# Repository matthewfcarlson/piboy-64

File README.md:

# Piboy-64
Original designed by Matthew Carlson
Huge shout out to /u/Ryzee and his GBA project here: https://github.com/Ryzee119/GBA_Emulator-by-Ryzee119-/blob/master/README.md

This is a true N64/PS1 emulator stuffed inside a GBA case. Based around a Raspberry Pi compute module 3 which is smaller but has the same guts as a RPi 3. A zero just didn't seem to cut it. Perhaps in the future, I'll do another version with the zero inside as well but for now I'll stick with this.

Details of how to build this and photos can be found on https://hackaday.io/project/17935-piboy-64

##DISCLAIMER:
This is a complex board with lots of parts. Make sure you know what you're doing. Surface mount soldering isn't hard but it is not for beginners. I used a third party replacement case for my GBA body and they vary from vendor to vendor so be flexible if what you have is different than what I did.

I take no responsibility for the following:

1.	You went ahead and purchased everything, soldered it up and it didn’t work because reasons.
2.	You soldered an SMD chip and done broke the pins.
3.	If a component in the BOM is not available or becomes obsolete, use your best judgement to find a replacement. I highly recommend parts.io which can provide risk factors and compatible chips.
4.	A component is missing from the BOM or you ordered parts you didn't need. (Look at the schematic before ordering)
5.	The thing burst into flame and explodes in your hands and burns your house down.
6.	It doesn’t fit in your GBA case

Any advice and support I provide from this point is purely out of the kindness of my heart.

## Issues Observed with this revision:
None yet

## Making your own
So you read this whole thing and still want to make your own? Well. Let's get started then. Visiting the hackaday.io link will give you detailed build instructions. I'll try and document as I go.

Good luck.

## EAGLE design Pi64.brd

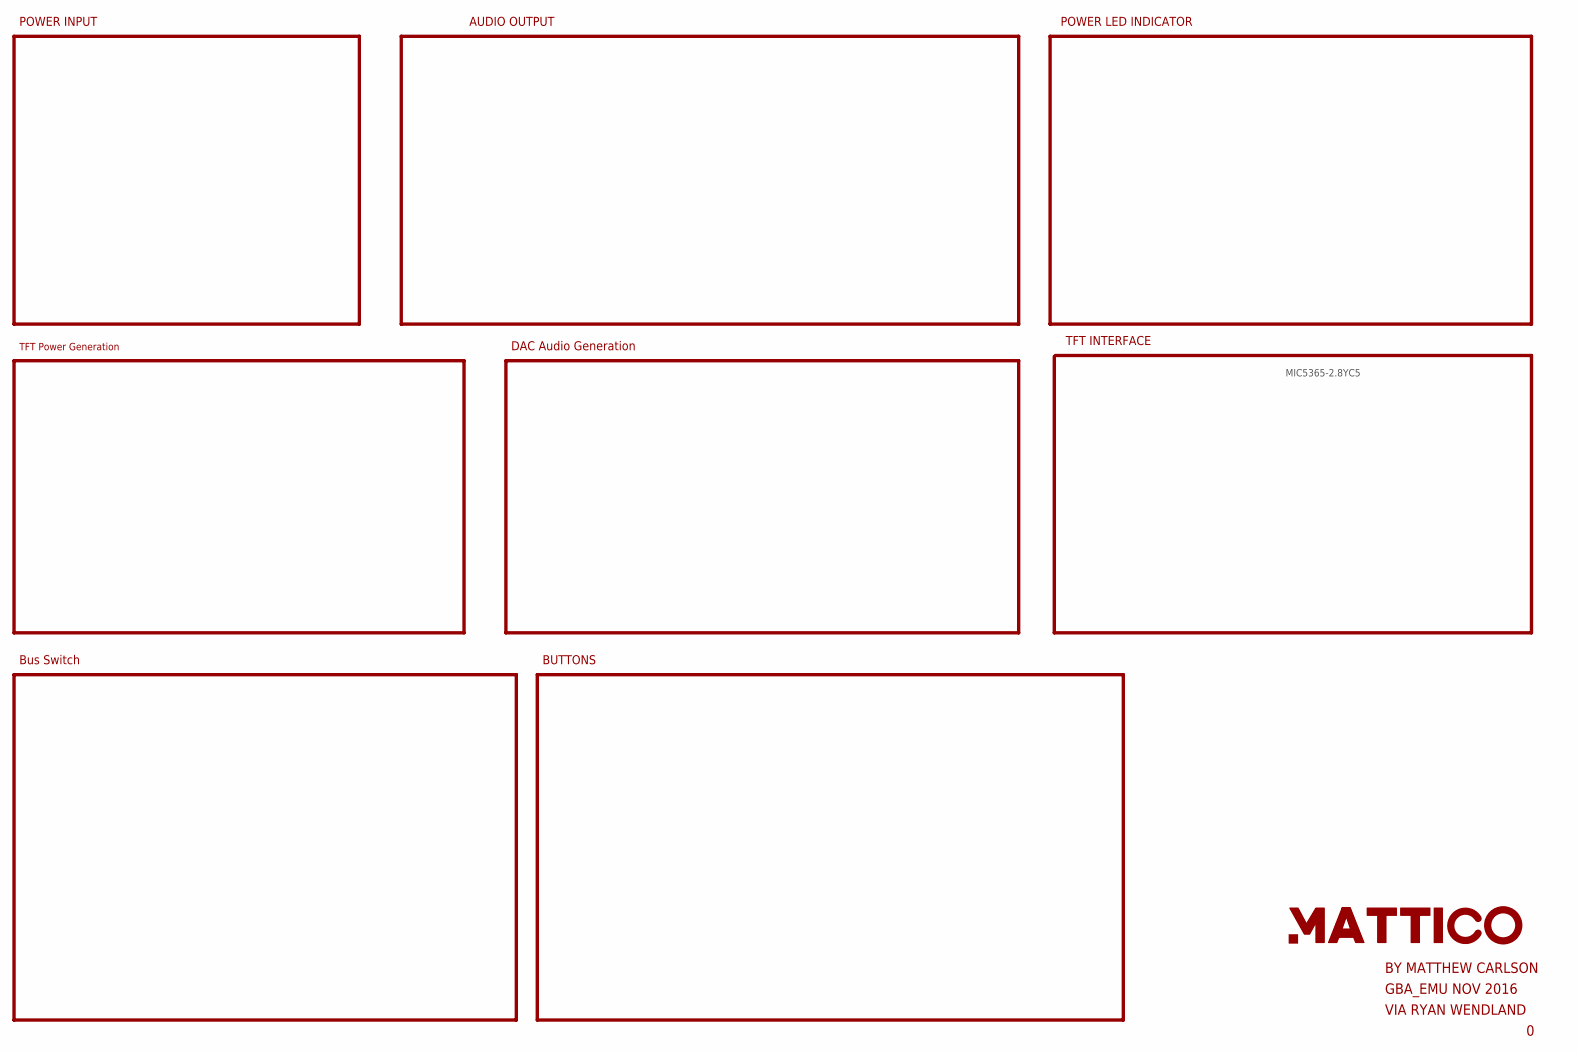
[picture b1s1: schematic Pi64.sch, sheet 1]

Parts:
U$2: LOGO2INCH_SVG; LOGO_2INCH_SVG

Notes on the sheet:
POWER LED INDICATOR
AUDIO OUTPUT
POWER INPUT
TFT INTERFACE
GBA_EMU NOV 2016
VIA RYAN WENDLAND
BY MATTHEW CARLSON
BUTTONS
MIC5365-2.8YC5
DAC Audio Generation
Bus Switch
TFT Power Generation

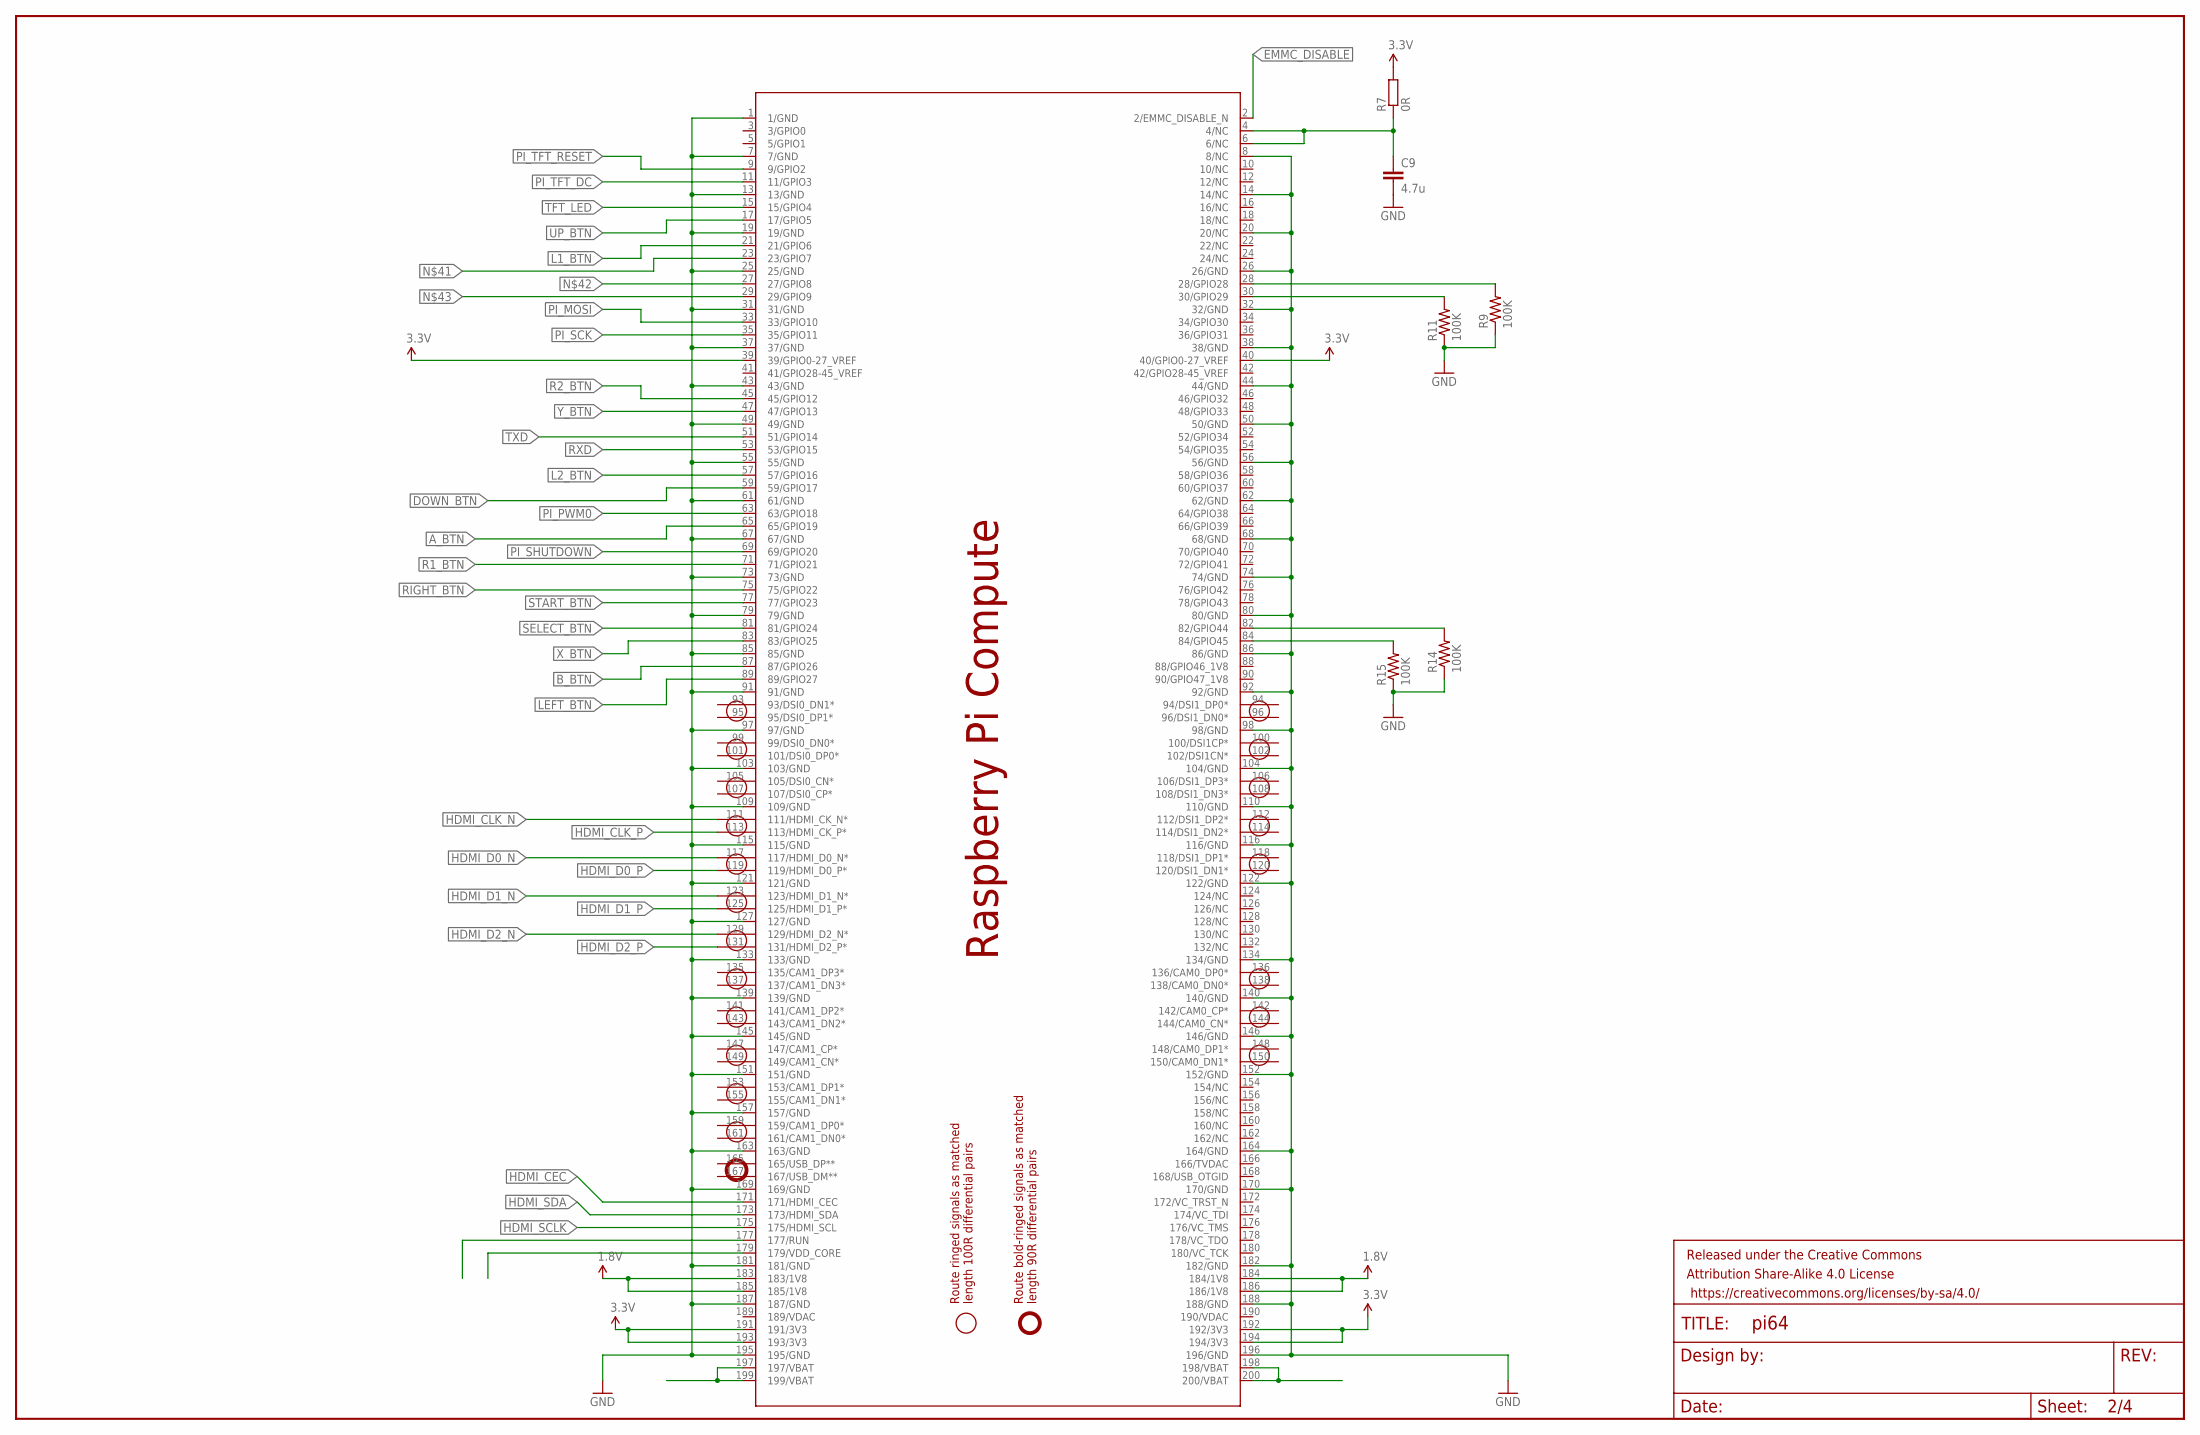
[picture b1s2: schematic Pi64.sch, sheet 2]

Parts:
C9: 4.7u; C1608
FRAME2: FRAME-LEDGER; CREATIVE_COMMONS
PCB1: RPI_COMPUTE
R7: 0R; R2012
R9, R11, R14, R15: 100K; R0805

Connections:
1.8V: PCB1.183 (183/1V8), PCB1.184 (184/1V8), PCB1.185 (185/1V8), PCB1.186 (186/1V8); also elsewhere on the board
3.3V: PCB1.39 (39/GPIO0-27_VREF), PCB1.40 (40/GPIO0-27_VREF), PCB1.191 (191/3V3), PCB1.192 (192/3V3), PCB1.193 (193/3V3), PCB1.194 (194/3V3), R7.2; also elsewhere on the board
A_BTN: PCB1.65 (65/GPIO19)
B_BTN: PCB1.87 (87/GPIO26)
DOWN_BTN: PCB1.59 (59/GPIO17)
EMMC_DISABLE: PCB1.2 (2/EMMC_DISABLE_N)
GND: C9.2, PCB1.1 (1/GND), PCB1.7 (7/GND), PCB1.8 (8/NC), PCB1.13 (13/GND), PCB1.14 (14/NC), PCB1.19 (19/GND), PCB1.20 (20/NC), PCB1.25 (25/GND), PCB1.26 (26/GND), PCB1.31 (31/GND), PCB1.32 (32/GND), PCB1.37 (37/GND), PCB1.38 (38/GND), PCB1.43 (43/GND), PCB1.44 (44/GND), PCB1.49 (49/GND), PCB1.50 (50/GND), PCB1.55 (55/GND), PCB1.56 (56/GND), PCB1.61 (61/GND), PCB1.62 (62/GND), PCB1.67 (67/GND), PCB1.68 (68/GND), PCB1.73 (73/GND), PCB1.74 (74/GND), PCB1.79 (79/GND), PCB1.80 (80/GND), PCB1.85 (85/GND), PCB1.86 (86/GND), PCB1.91 (91/GND), PCB1.92 (92/GND), PCB1.97 (97/GND), PCB1.98 (98/GND), PCB1.103 (103/GND), PCB1.104 (104/GND), PCB1.109 (109/GND), PCB1.110 (110/GND), PCB1.115 (115/GND), PCB1.116 (116/GND), PCB1.121 (121/GND), PCB1.122 (122/GND), PCB1.127 (127/GND), PCB1.133 (133/GND), PCB1.134 (134/GND), PCB1.139 (139/GND), PCB1.140 (140/GND), PCB1.145 (145/GND), PCB1.146 (146/GND), PCB1.151 (151/GND), PCB1.152 (152/GND), PCB1.157 (157/GND), PCB1.163 (163/GND), PCB1.164 (164/GND), PCB1.169 (169/GND), PCB1.170 (170/GND), PCB1.181 (181/GND), PCB1.182 (182/GND), PCB1.187 (187/GND), PCB1.188 (188/GND), PCB1.195 (195/GND), PCB1.196 (196/GND), R9.1, R11.1, R14.1, R15.1; also elsewhere on the board
HDMI_CEC: PCB1.171 (171/HDMI_CEC)
HDMI_CLK_N: PCB1.111 (111/HDMI_CK_N*)
HDMI_CLK_P: PCB1.113 (113/HDMI_CK_P*)
HDMI_D0_N: PCB1.117 (117/HDMI_D0_N*)
HDMI_D0_P: PCB1.119 (119/HDMI_D0_P*)
HDMI_D1_N: PCB1.123 (123/HDMI_D1_N*)
HDMI_D1_P: PCB1.125 (125/HDMI_D1_P*)
HDMI_D2_N: PCB1.129 (129/HDMI_D2_N*)
HDMI_D2_P: PCB1.131 (131/HDMI_D2_P*)
HDMI_SCLK: PCB1.175 (175/HDMI_SCL)
HDMI_SDA: PCB1.173 (173/HDMI_SDA)
L1_BTN: PCB1.21 (21/GPIO6)
L2_BTN: PCB1.57 (57/GPIO16)
LEFT_BTN: PCB1.89 (89/GPIO27)
unnamed: C9.1, PCB1.4 (4/NC), PCB1.6 (6/NC), R7.1
unnamed: PCB1.28 (28/GPIO28), R9.2
unnamed: PCB1.30 (30/GPIO29), R11.2
unnamed: PCB1.197 (197/VBAT), PCB1.199 (199/VBAT)
unnamed: PCB1.198 (198/VBAT), PCB1.200 (200/VBAT)
PI_MOSI: PCB1.33 (33/GPIO10)
PI_PWM0: PCB1.63 (63/GPIO18)
PI_SCK: PCB1.35 (35/GPIO11)
PI_SHUTDOWN: PCB1.69 (69/GPIO20)
PI_TFT_DC: PCB1.11 (11/GPIO3)
PI_TFT_RESET: PCB1.9 (9/GPIO2)
R1_BTN: PCB1.71 (71/GPIO21)
R2_BTN: PCB1.45 (45/GPIO12)
RIGHT_BTN: PCB1.75 (75/GPIO22)
RXD: PCB1.53 (53/GPIO15)
SELECT_BTN: PCB1.81 (81/GPIO24)
START_BTN: PCB1.77 (77/GPIO23)
TFT_LED: PCB1.15 (15/GPIO4)
TXD: PCB1.51 (51/GPIO14)
UP_BTN: PCB1.17 (17/GPIO5)
X_BTN: PCB1.83 (83/GPIO25)
Y_BTN: PCB1.47 (47/GPIO13)

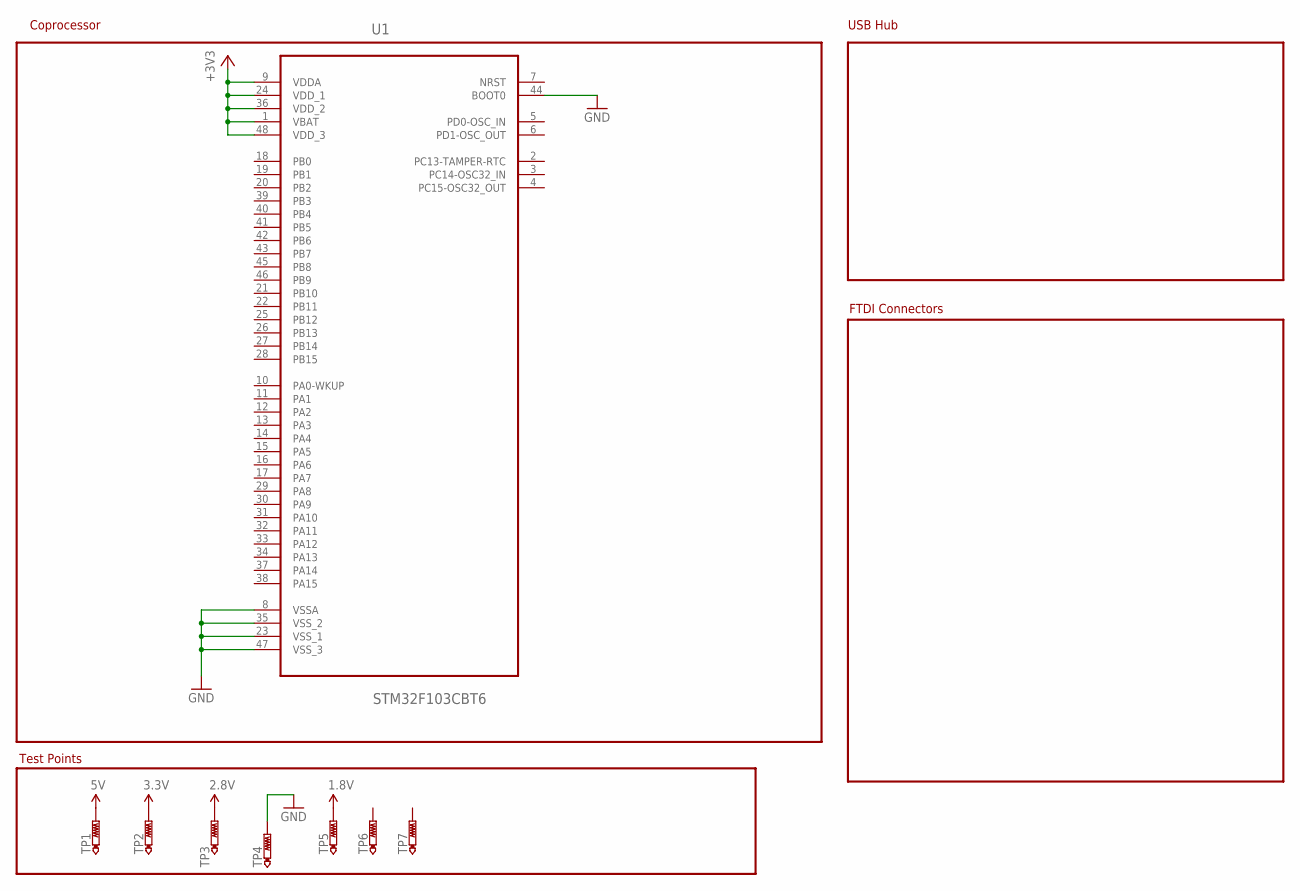
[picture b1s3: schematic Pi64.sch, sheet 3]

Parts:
TP1, TP2, TP3, TP4, TP5, TP6, TP7: PTR1TP12R; TP12R
U1: STM32F103CBT6; QFP50P900X900X160-48N

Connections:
1.8V: TP5.TP; also elsewhere on the board
2.8V: TP3.TP
3.3V: TP2.TP; also elsewhere on the board
5V: TP1.TP
+3V3: U1.1 (VBAT), U1.9 (VDDA), U1.24 (VDD_1), U1.36 (VDD_2), U1.48 (VDD_3)
GND: TP4.TP, U1.8 (VSSA), U1.23 (VSS_1), U1.35 (VSS_2), U1.44 (BOOT0), U1.47 (VSS_3); also elsewhere on the board
PA11: U1.32 (PA11)

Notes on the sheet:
Coprocessor
USB Hub
FTDI Connectors
Test Points

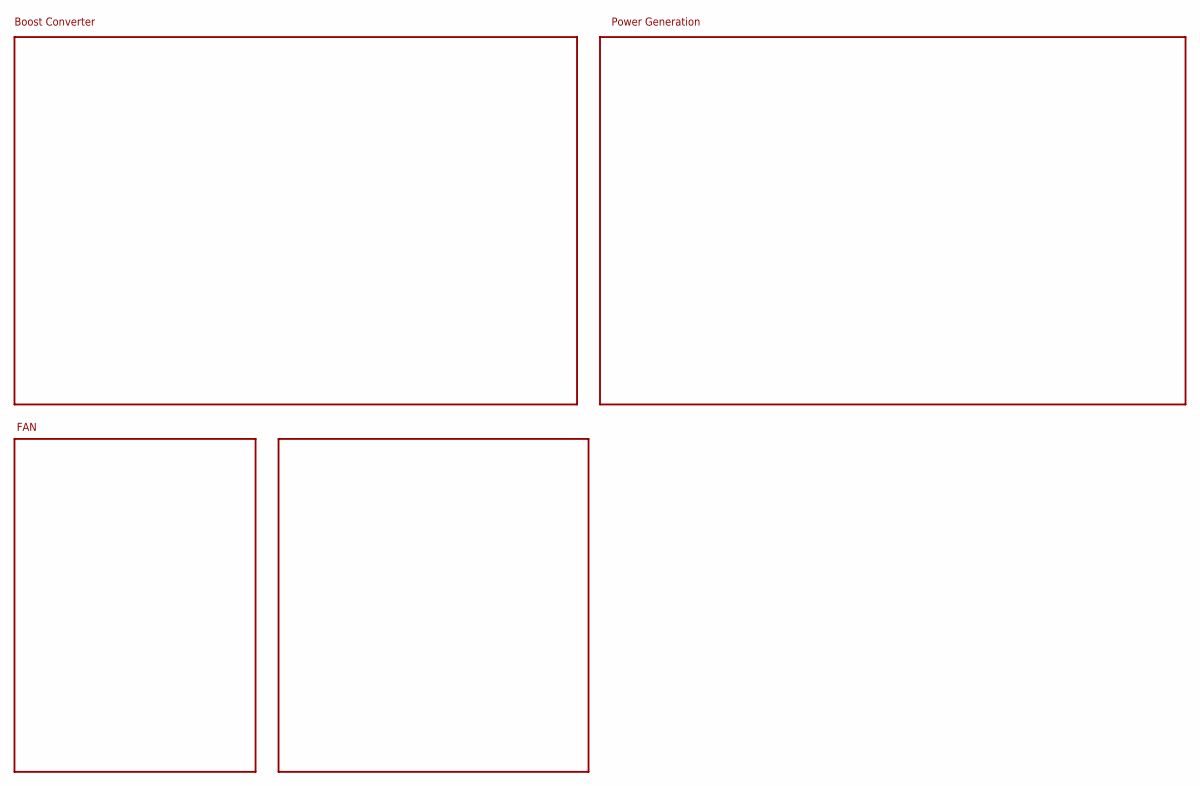
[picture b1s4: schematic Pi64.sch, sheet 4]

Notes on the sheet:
Boost Converter
Power Generation
FAN

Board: 2 copper layers, 18 parts (2 on the bottom side), 9 nets, no tracks yet.

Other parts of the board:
U$7: LOGO2INCH_SVG; LOGO_2INCH_SVG

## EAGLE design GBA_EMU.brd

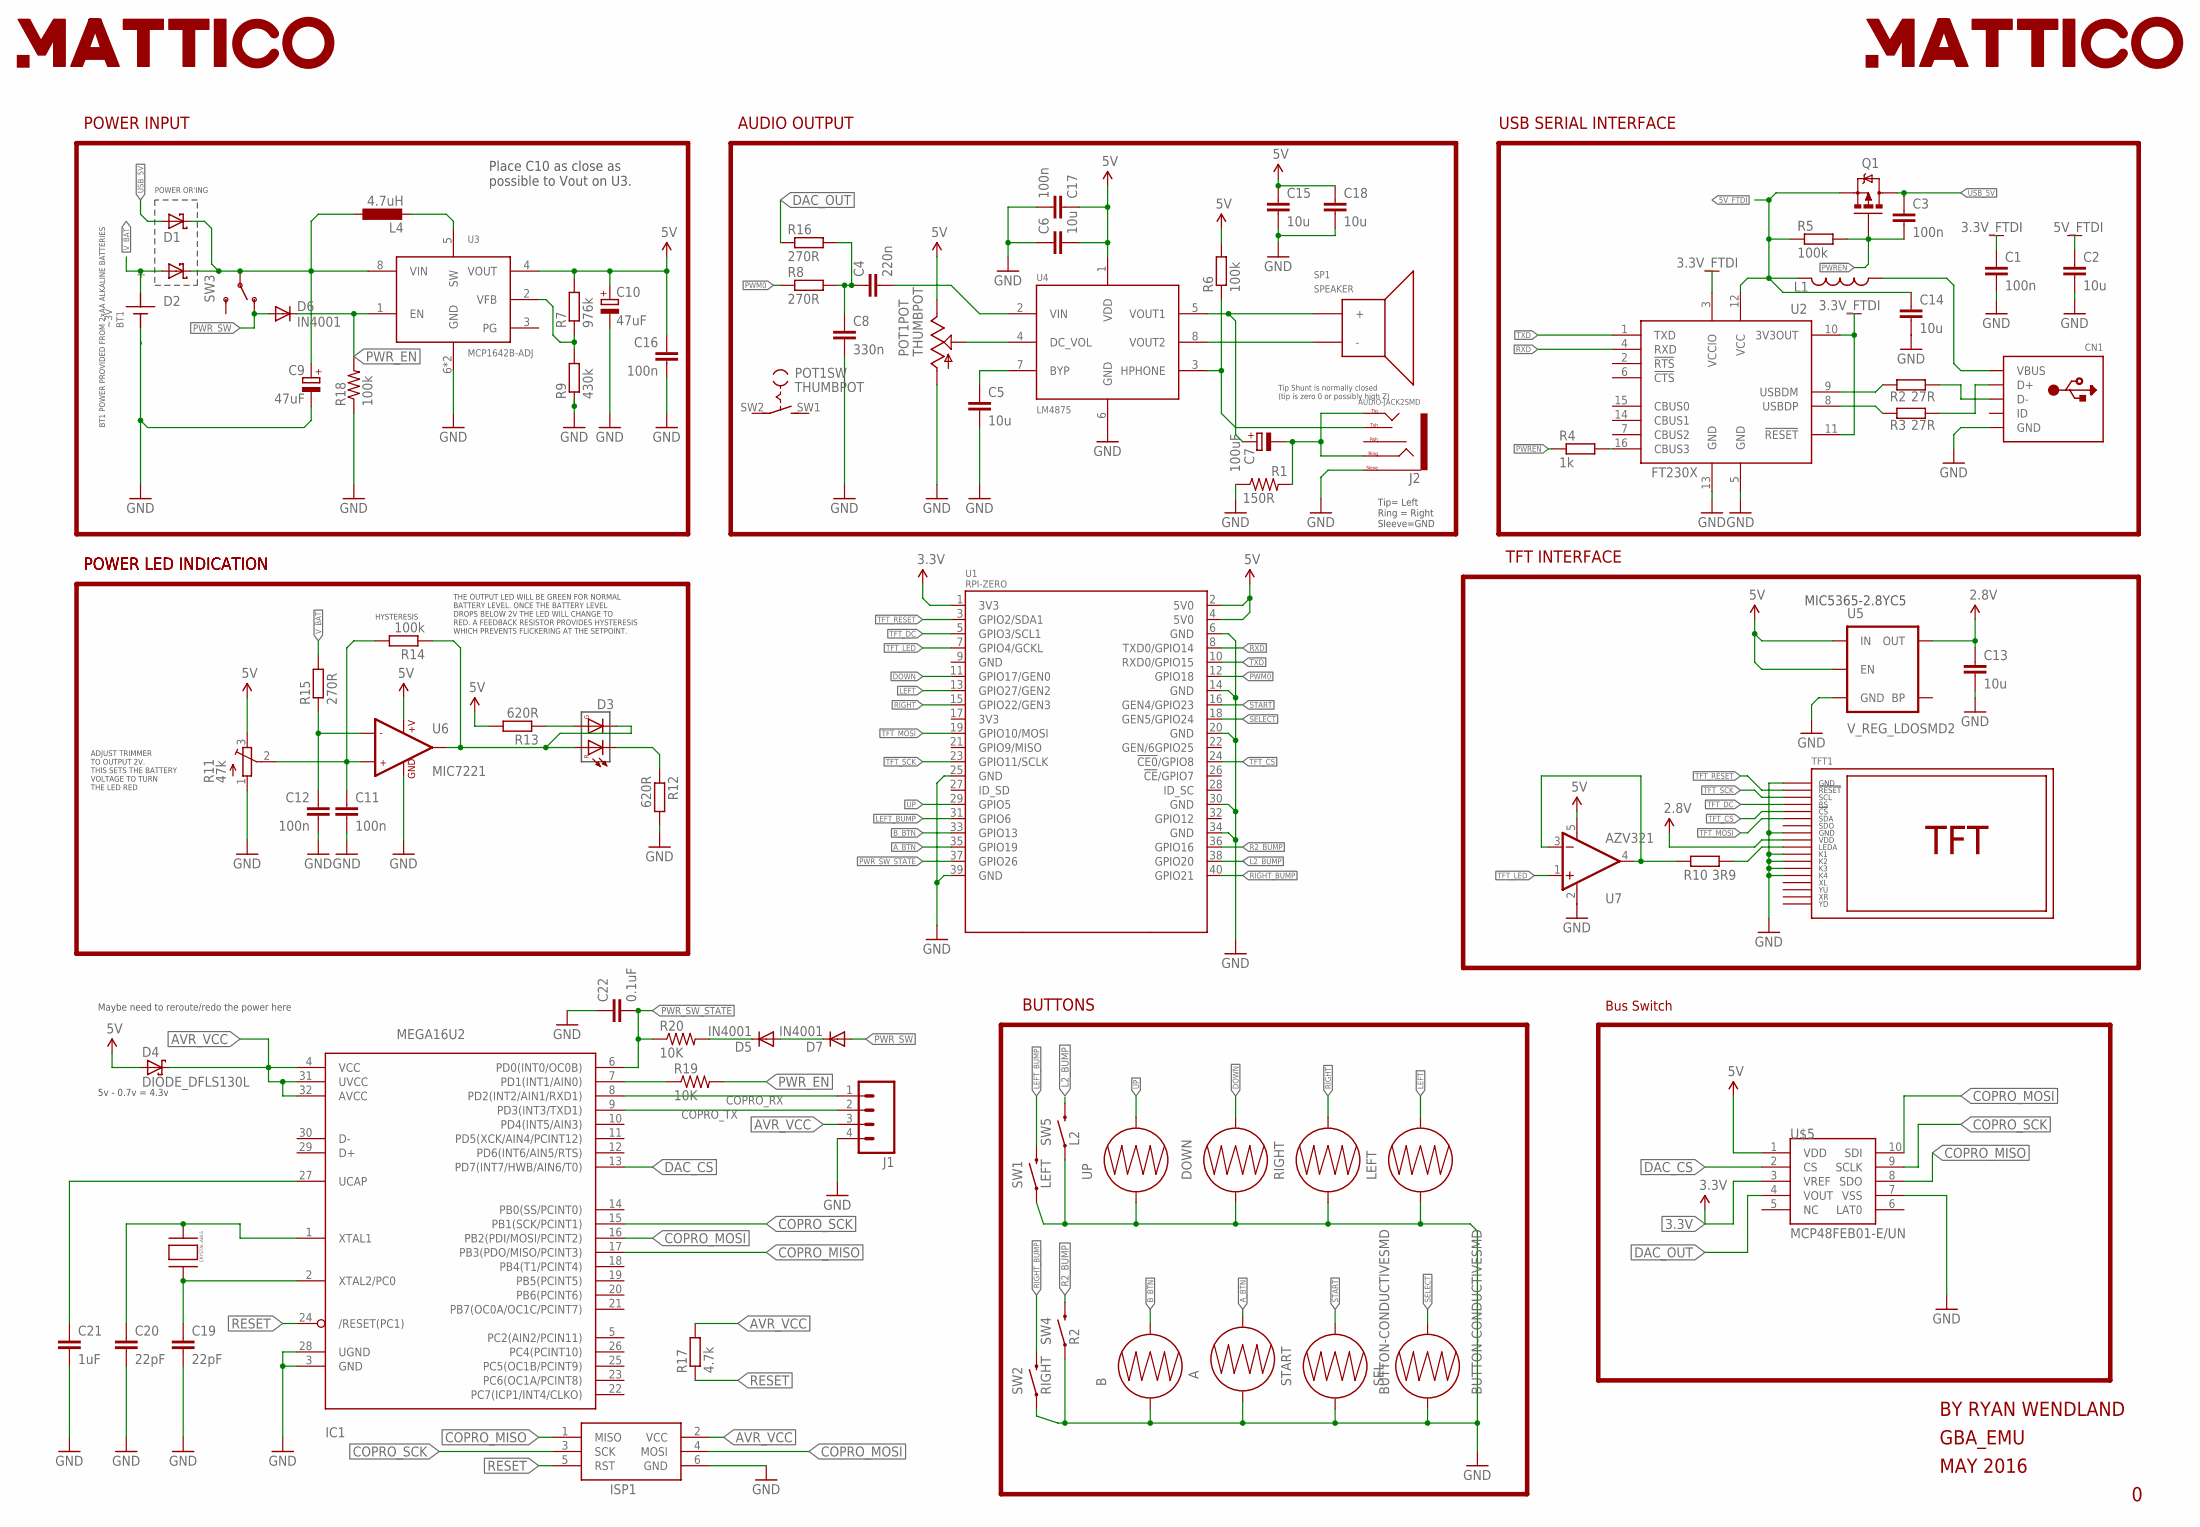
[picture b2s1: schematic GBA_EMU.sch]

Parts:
A: GBA_BTN_CONDUCTIVE; GBA_BUTTON_CONDUCTIVE
B: GBA_BTN_CONDUCTIVE; GBA_BUTTON_CONDUCTIVE
BT1: ~3V; BATTERY
C1, C3, C11, C12, C16, C17: 100n; C0805
C2, C5, C6, C13, C14, C15, C18: 10u; C0805
C4: 220n; C0805
C7: 100uF; 153CLV-0405
C8: 330n; C0805
C9, C10: 47uF; 153CLV-0405
C19, C20: 22pF; 0603-CAP
C21: 1uF; 0805-CAP
C22: 0.1uF; 0603-CAP
CN1: USBMINIB; USB-MINIB
D1, D2: DFLS130L; POWERDI_123
D3: DUAL_LED
D4: DIODE_DFLS130L; DIODE_POWERDI_123
D5, D6, D7: IN4001; SOD-123_MINI-SMA
DOWN: GBA_BTN_CONDUCTIVE; GBA_BUTTON_CONDUCTIVE
IC1: MEGA16U2; TQFP32-08
ISP1: AVRISP-6; AVRISP
J1: M041.27MM; 1X04-1.27MM
J2: AUDIO-JACK2SMD; AUDIO-JACK-3.5MM-SMD
L1: 600; 0805
L4: 4.7uH; POWER-CHOKE_WE-TPC
LEFT: GBA_BTN_CONDUCTIVE; GBA_BUTTON_CONDUCTIVE
POT1: THUMBPOT; THUMBWHEEL
Q1: MOSFET-PCHANNEL; SOT23-3
R1: 150R; 0603-RES
R2, R3: 27R; R0805
R4: 1k; R0805
R5, R6, R14: 100k; R0805
R7: 976k; R0805
R8, R15, R16: 270R; R0805
R9: 430k; R0805
R10: 3R9; R0805
R11: 47k; TC33X
R12, R13: 620R; R0805
R17: 4.7k; R0805
R18: 100k; 0603-RES
R19, R20: 10K; 0603-RES
RIGHT: GBA_BTN_CONDUCTIVE; GBA_BUTTON_CONDUCTIVE
SEL: BUTTON-CONDUCTIVESMD; BUTTON-CONDUCTIVE
SP1: SPEAKER
START: BUTTON-CONDUCTIVESMD; BUTTON-CONDUCTIVE
SW1: LEFT; BUMPER
SW2: RIGHT; BUMPER
SW3: GBA_PWR_SWITCHCSS_1310TB; PWR_SWITCH_CSS_1310TB
SW4: R2; BUMPER_NOHOLE
SW5: L2; BUMPER_NOHOLE
TFT1: GBA_TFT
U1: RPI-ZERO; RASPBERRYPI_BASTELSTUBE_V13_RASPI_BOARD_B+_FULL
U2: FT230X; SSOP16
U3: MCP1642B-ADJ; MSOP8
U4: LM4875; SOIC8
U5: V_REG_LDOSMD2; SC70
U6: MIC7221; SOT23-5
U7: AZV321; SOT23-5
U$1, U$2: LOGO2INCH_SVG; LOGO_2INCH_SVG
U$3: CRYSTAL-ABLS; HC49/US
U$5: MCP48FEB01-E/UN; 10-MSOP
UP: GBA_BTN_CONDUCTIVE; GBA_BUTTON_CONDUCTIVE

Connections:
0.8128: C9.+, D1.2 (C), D2.2 (C), L4.1, SW3.P$3, U3.8 (VIN)
2.8V: C13.1, TFT1.9 (VDD), U5.5 (OUT)
3.3V: U1.1 (3V3), U$5.3 (VREF)
3.3V_FTDI: C1.1, U2.3 (VCCIO), U2.10 (3V3OUT), U2.11 (!RESET)
5V: C6.2, C10.+, C15.1, C16.1, C17.1, C18.1, D4.1 (A), POT1.3 (E), R6.2, R7.2, R11.3 (E), R13.2, U1.2 (5V0), U1.4 (5V0), U3.4 (VOUT), U4.1 (VDD), U5.1 (IN), U5.3 (EN), U6.2 (+V), U7.5 (V+), U$5.1 (VDD)
5V_FTDI: C2.1, C14.1, L1.1, Q1.2 (S), R5.1, U2.12 (VCC)
!PWREN: C3.2, Q1.1 (G), R4.1, R5.2
AVR_VCC: D4.2 (C), IC1.4 (VCC), IC1.31 (UVCC), IC1.32 (AVCC), ISP1.2 (VCC), J1.3, R17.2
A_BTN: A.2, U1.35 (GPIO19)
B_BTN: B.2, U1.33 (GPIO13)
COPRO_MISO: IC1.17 (PB3(PDO/MISO/PCINT3)), ISP1.1 (MISO), U$5.8 (SDO)
COPRO_MOSI: IC1.16 (PB2(PDI/MOSI/PCINT2)), ISP1.4 (MOSI), U$5.10 (SDI)
COPRO_RX: IC1.8 (PD2(INT2/AIN1/RXD1)), J1.1
COPRO_SCK: IC1.15 (PB1(SCK/PCINT1)), ISP1.3 (SCK), U$5.9 (SCLK)
COPRO_TX: IC1.9 (PD3(INT3/TXD1)), J1.2
DAC_CS: IC1.13 (PD7(INT7/HWB/AIN6/T0)), U$5.2 (CS)
DAC_OUT: R16.1, U$5.4 (VOUT)
DOWN: DOWN.2, U1.11 (GPIO17/GEN0)
GND: A.1, B.1, BT1.BT-1 (-), BT1.BT-2 (-), C1.2, C2.2, C5.2, C6.1, C8.2, C9.-, C10.-, C11.2, C12.2, C13.2, C14.2, C15.2, C16.2, C17.2, C18.2, C19.2, C20.2, C21.2, C22.1, CN1.GND, DOWN.1, IC1.3 (GND), IC1.28 (UGND), ISP1.6 (GND), J1.4, J2.SLEEVE, LEFT.1, POT1.1 (A), R1.1, R9.1, R11.1 (A), R12.2, R18.1, RIGHT.1, SEL.1, START.1, SW1.1, SW2.1, SW4.1, SW5.1, TFT1.1 (GND), TFT1.8 (GND), TFT1.11 (K1), TFT1.12 (K2), TFT1.13 (K3), TFT1.14 (K4), U1.6 (GND), U1.14 (GND), U1.20 (GND), U1.25 (GND), U1.30 (GND), U1.34 (GND), U1.39 (GND), U2.5 (GND), U2.13 (GND), U3.6 (GND), U3.7 (GND), U4.6 (GND), U5.2 (GND), U6.5 (GND), U7.2 (V-), U$5.7 (VSS), UP.1
L2_BUMP: SW5.2, U1.38 (GPIO20)
LEFT: LEFT.2, U1.13 (GPIO27/GEN2)
LEFT_BUMP: SW1.2, U1.31 (GPIO6)
unnamed: C11.1, R11.2 (S), R14.2, U6.3 (+IN1)
unnamed: C4.1, C8.1, R8.2, R16.2
unnamed: CN1.VBUS, L1.2
unnamed: CN1.D-, R2.2
unnamed: CN1.D+, R3.2
unnamed: R2.1, U2.9 (USBDM)
unnamed: R3.1, U2.8 (USBDP)
unnamed: POT1.2 (S), U4.4 (DC_VOL)
unnamed: C4.2, U4.2 (VIN)
unnamed: R4.2, U2.16 (CBUS3)
unnamed: C5.1, U4.7 (BYP)
unnamed: L4.2, U3.5 (SW)
unnamed: D5.A, D7.C
unnamed: C7.+, SP1.1 (+), U4.5 (VOUT1)
unnamed: SP1.2 (-), U4.8 (VOUT2)
unnamed: J2.TSH, R6.1, U4.3 (HPHONE)
unnamed: C20.1, IC1.1 (XTAL1), U$3.P$2
unnamed: IC1.7 (PD1(INT1/AIN0)), R19.1
unnamed: D3.1, D3.3, R14.1, U6.1 (OUT1)
unnamed: R7.1, R9.2, U3.2 (VFB)
unnamed: R10.2, TFT1.10 (LEDA)
unnamed: D3.4, R13.1
unnamed: D3.2, R12.1
unnamed: R10.1, U7.3 (-IN), U7.4 (OUT)
unnamed: C12.1, R15.1, U6.4 (-IN1)
unnamed: C19.1, IC1.2 (XTAL2/PC0), U$3.P$1
unnamed: C21.1, IC1.27 (UCAP)
unnamed: C7.-, J2.RING, J2.TIP, R1.2
unnamed: D5.C, R20.2
PWM0: R8.1, U1.12 (GPIO18)
PWR_EN: D6.C, R18.2, R19.2, U3.1 (EN)
PWR_SW: D6.A, D7.A, SW3.P$1 (O)
PWR_SW_STATE: C22.2, IC1.6 (PD0(INT0/OC0B)), R20.1, U1.37 (GPIO26)
R2_BUMP: SW4.2, U1.36 (GPIO16)
RESET: IC1.24 (/RESET(PC1)), ISP1.5 (RST), R17.1
RIGHT: RIGHT.2, U1.15 (GPIO22/GEN3)
RIGHT_BUMP: SW2.2, U1.40 (GPIO21)
RXD: U1.8 (TXD0/GPIO14), U2.4 (RXD)
SELECT: SEL.2, U1.18 (GEN5/GPIO24)
START: START.2, U1.16 (GEN4/GPIO23)
TFT_CS: TFT1.5 (!CS), U1.24 (!CE0!/GPIO8)
TFT_DC: TFT1.4 (RS), U1.5 (GPIO3/SCL1)
TFT_LED: U1.7 (GPIO4/GCKL), U7.1 (+IN)
TFT_MOSI: TFT1.6 (SDA), U1.19 (GPIO10/MOSI)
TFT_RESET: TFT1.2 (!RESET), U1.3 (GPIO2/SDA1)
TFT_SCK: TFT1.3 (SCL), U1.23 (GPIO11/SCLK)
TXD: U1.10 (RXD0/GPIO15), U2.1 (TXD)
UP: U1.29 (GPIO5), UP.2
USB_5V: C3.1, D1.1 (A), Q1.3 (D)
V_BAT: BT1.BT+1 (+), BT1.BT+2 (+), D2.1 (A), R15.2

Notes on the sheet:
USB SERIAL INTERFACE
AUDIO OUTPUT
POWER INPUT
POWER OR'ING
BT1 POWER PROVIDED FROM 2xAA ALKALINE BATTERIES
TFT INTERFACE
ADJUST TRIMMER TO OUTPUT 2V. THIS SETS THE BATTERY VOLTAGE TO TURN THE LED RED
HYSTERESIS
POWER LED INDICATION
THE OUTPUT LED WILL BE GREEN FOR NORMAL BATTERY LEVEL. ONCE THE BATTERY LEVEL DROPS BELOW 2V THE LED WILL CHANGE TO RED. A FEEDBACK RESISTOR PROVIDES HYSTERESIS WHICH PREVENTS FLICKERING AT THE SETPOINT.
GBA_EMU
MAY 2016
BY RYAN WENDLAND
BUTTONS
Place C10 as close as possible to Vout on U3.
MIC5365-2.8YC5
Bus Switch
Maybe need to reroute/redo the power here
Tip= Left Ring = Right Sleeve=GND
Tip Shunt is normally closed (tip is zero 0 or possibly high Z)
5v - 0.7v = 4.3v

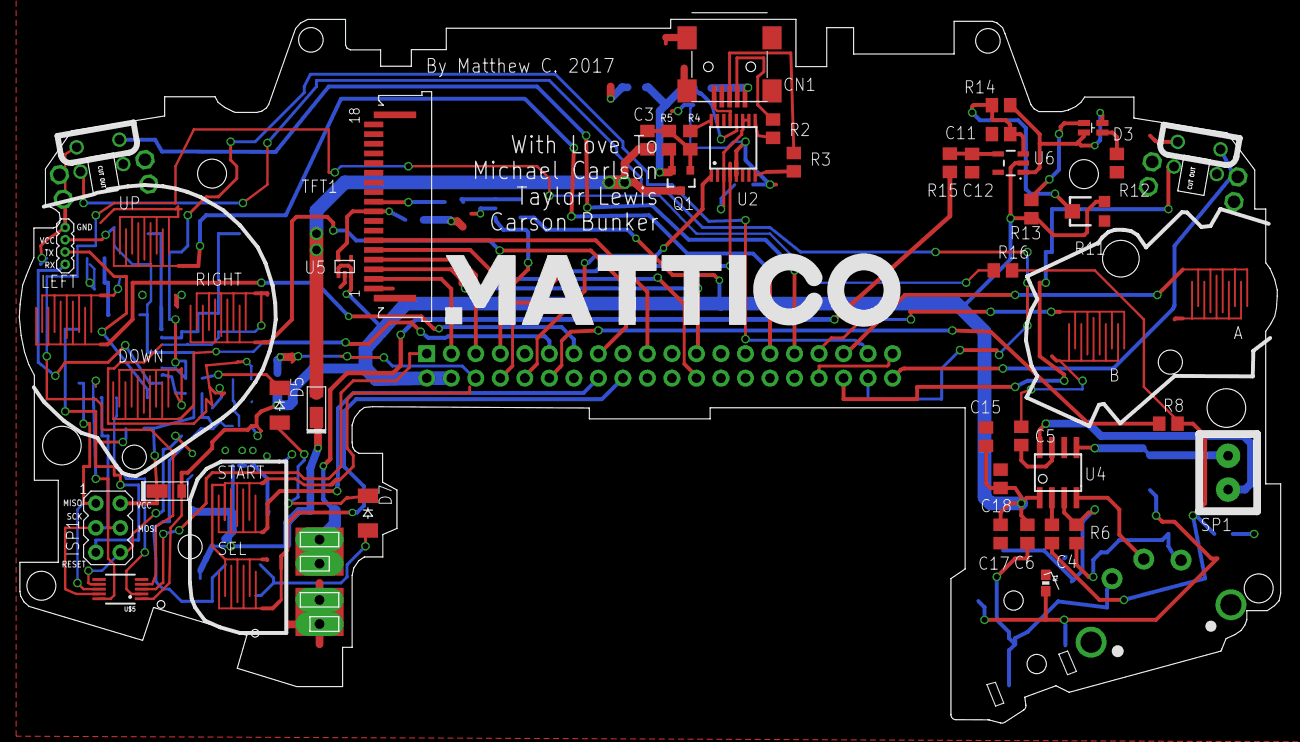
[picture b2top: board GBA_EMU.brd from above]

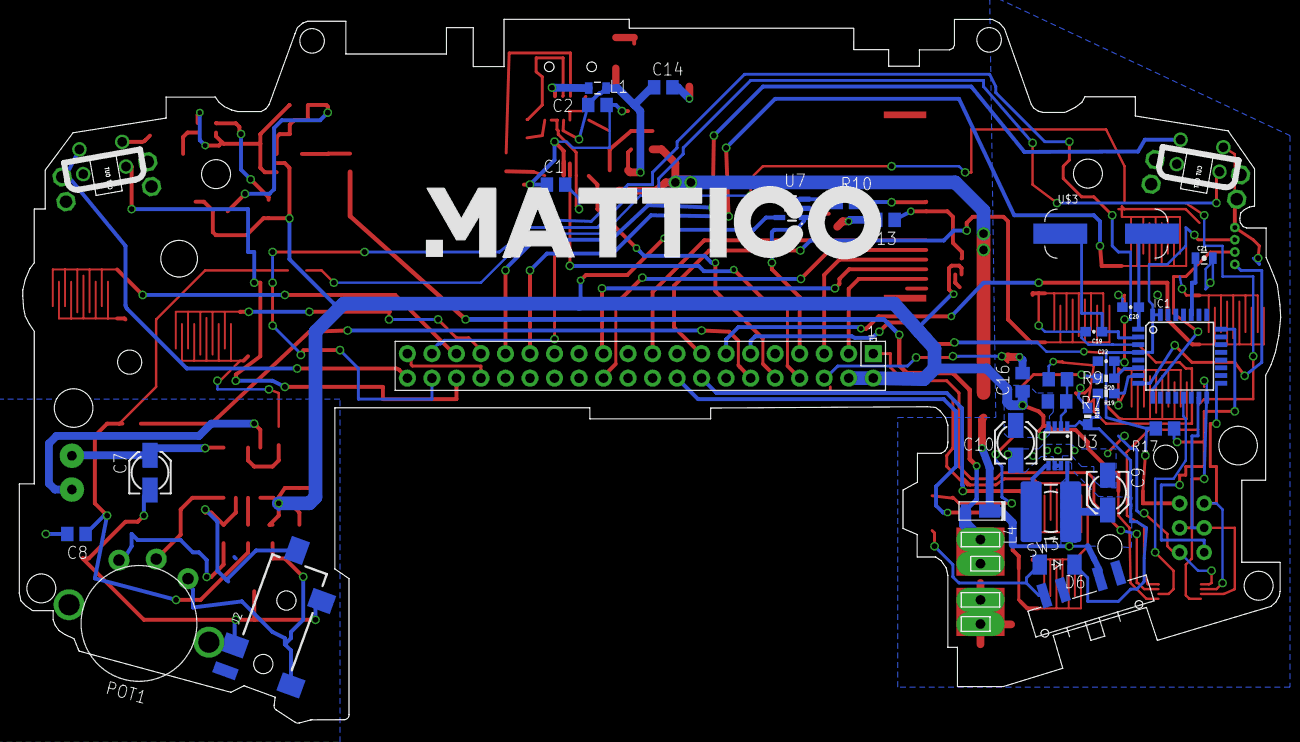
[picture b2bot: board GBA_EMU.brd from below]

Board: 2 copper layers, 130.7 x 72.9 mm, 85 parts (35 on the bottom side), 72 nets.

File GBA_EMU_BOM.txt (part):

Partlist exported from C:/Users/matth/GitHub/piboy-64/GBA_EMU.sch at 11/21/2017 6:22 PM

Part  Value                Device                    Package                                         Description                                                                                               PROD_ID     VALUE
A     GBA_BTN_CONDUCTIVE   GBA_BTN_CONDUCTIVE        GBA_BUTTON_CONDUCTIVE                                                                                                                                                      
B     GBA_BTN_CONDUCTIVE   GBA_BTN_CONDUCTIVE        GBA_BUTTON_CONDUCTIVE                                                                                                                                                      
BT1   ~3V                  BATTERY                   BATTERY                                                                                                                                                                    
C1    100n                 C-EUC0805                 C0805                                           CAPACITOR, European symbol                                                                                                 
C2    10u                  C-EUC0805                 C0805                                           CAPACITOR, European symbol                                                                                                 
C3    100n                 C-EUC0805                 C0805                                           CAPACITOR, European symbol                                                                                                 
C4    220n                 C-EUC0805                 C0805                                           CAPACITOR, European symbol                                                                                                 
C5    10u                  C-EUC0805                 C0805                                           CAPACITOR, European symbol                                                                                                 
C6    10u                  C-EUC0805                 C0805                                           CAPACITOR, European symbol                                                                                                 
C7    100uF                CPOL-EU153CLV-0405        153CLV-0405                                     POLARIZED CAPACITOR, European symbol                                                                                       
C8    330n                 C-EUC0805                 C0805                                           CAPACITOR, European symbol                                                                                                 
C9    47uF                 CPOL-EU153CLV-0405        153CLV-0405                                     POLARIZED CAPACITOR, European symbol                                                                                       
C10   47uF                 CPOL-EU153CLV-0405        153CLV-0405                                     POLARIZED CAPACITOR, European symbol                                                                                       
C11   100n                 C-EUC0805                 C0805                                           CAPACITOR, European symbol                                                                                                 
C12   100n                 C-EUC0805                 C0805                                           CAPACITOR, European symbol                                                                                                 
C13   10u                  C-EUC0805                 C0805                                           CAPACITOR, European symbol                                                                                                 
C14   10u                  C-EUC0805                 C0805                                           CAPACITOR, European symbol                                                                                                 
C15   10u                  C-EUC0805                 C0805                                           CAPACITOR, European symbol                                                                                                 
C16   100n                 C-EUC0805                 C0805                                           CAPACITOR, European symbol                                                                                                 
C17   100n                 C-EUC0805                 C0805                                           CAPACITOR, European symbol                                                                                                 
C18   10u                  C-EUC0805                 C0805                                           CAPACITOR, European symbol                                                                                                 
C19   22pF                 22PF-50V-5%(0603)         0603-CAP                                        CAP-07876                                                                                                 CAP-07876   22pF 
C20   22pF                 22PF-50V-5%(0603)         0603-CAP                                        CAP-07876                                                                                                 CAP-07876   22pF 
C21   1uF                  1UF-25V-10%(0805)"        0805-CAP                                        CAP-08064                                                                                                                  
C22   0.1uF                0.1UF-25V(+80/-20%)(0603) 0603-CAP                                        CAP-00810                                                                                                 CAP-00810   0.1uF
CN1                        USBMINIB                  USB-MINIB                                       USB Connectors                                                                                                             
D1    DFLS130L             DFLS130L                  POWERDI_123                                                                                                                                                                
D2    DFLS130L             DFLS130L                  POWERDI_123                                                                                                                                                                
D3    DUAL_LED             DUAL_LED                  DUAL_LED                                                                                                                                                                   
D4    DIODE_DFLS130L       DIODE_DFLS130L            DIODE_POWERDI_123                                                                                                                                                          
D5    IN4001               CGRM4001-G                SOD-123_MINI-SMA                                Molded plasitc,JEDEC SOD-123/Mini SMA                                                                                      
D6    IN4001               CGRM4001-G                SOD-123_MINI-SMA                                Molded plasitc,JEDEC SOD-123/Mini SMA                                                                                      
D7    IN4001               CGRM4001-G                SOD-123_MINI-SMA                                Molded plasitc,JEDEC SOD-123/Mini SMA                                                                                      
DOWN  GBA_BTN_CONDUCTIVE   GBA_BTN_CONDUCTIVE        GBA_BUTTON_CONDUCTIVE                                                                                                                                                      
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

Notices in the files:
parts and their libraries:
SparkFun-Electromechanical: Licensing: Creative Commons ShareAlike 4.0 International - https://creativecommons.org/licenses/by-sa/4.0
SparkFun-Aesthetics: Released under the Creative Commons Attribution Share-Alike 4.0 License
SparkFun-Aesthetics: https://creativecommons.org/licenses/by-sa/4.0
